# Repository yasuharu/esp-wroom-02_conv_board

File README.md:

# Schematic of pitch conversion board for ESP-WROOM-02 with EAGLE
## About

This repository includes schematic of pitch conversion board for ESP-WROOM-02 with EAGLE.
This data can make the board by PCB Manufacture(I used Switch-Science).

## About data

The schematics use following files :

 * Supplied from Switch-Science
  * SeeedStudio_2layer_DRU_no_angle_20140221a.dru
  * Seeed_Gerber_Generater_2-layer.cam
 * ESP-WROOM-02 library data(URL : http://qiita.com/ikesato/items/92f4cb143e7aeb5e0f9b)
  * esp-wroom-02.lbr
  * Thank you for releasing it!!
 * pinhead.lbr
  * Copy from EAGLE library

esp-wroom-02.lbr and pinhead.lbr are fixed because of silk data is not good.
(I didn't know those license so that it not commit this repository.)

## Author

Yasuharu Shibata
http://yasuharu.net

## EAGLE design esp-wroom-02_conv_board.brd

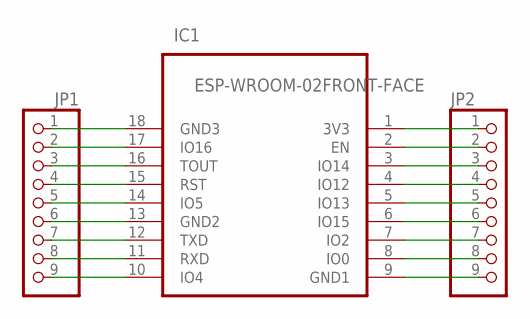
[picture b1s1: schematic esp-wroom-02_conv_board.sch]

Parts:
IC1: ESP-WROOM-02FRONT-FACE; FRONT-FACE
JP1, JP2: PINHD-1X9; 1X09

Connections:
unnamed: IC1.10 (IO4), JP1.9
unnamed: IC1.11 (RXD), JP1.8
unnamed: IC1.12 (TXD), JP1.7
unnamed: IC1.13 (GND2), JP1.6
unnamed: IC1.14 (IO5), JP1.5
unnamed: IC1.15 (RST), JP1.4
unnamed: IC1.16 (TOUT), JP1.3
unnamed: IC1.17 (IO16), JP1.2
unnamed: IC1.18 (GND3), JP1.1
unnamed: IC1.1 (3V3), JP2.1
unnamed: IC1.2 (EN), JP2.2
unnamed: IC1.3 (IO14), JP2.3
unnamed: IC1.4 (IO12), JP2.4
unnamed: IC1.5 (IO13), JP2.5
unnamed: IC1.6 (IO15), JP2.6
unnamed: IC1.7 (IO2), JP2.7
unnamed: IC1.8 (IO0), JP2.8
unnamed: IC1.9 (GND1), JP2.9

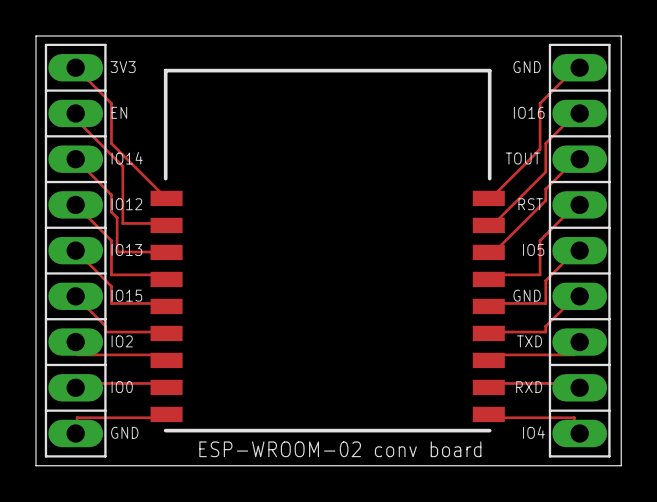
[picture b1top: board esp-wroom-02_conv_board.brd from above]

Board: 2 copper layers, 32.5 x 23.9 mm, 3 parts (0 on the bottom side), 18 nets.

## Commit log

2015-09-24 * add first files.
2015-09-24 * add explanation of this repository
2015-09-24 * Add pdf preview files.
